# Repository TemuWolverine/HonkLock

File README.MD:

- [Electronics](#electronics)
  - [Brain board](#brain-board)
  - [Sensor Board](#sensor-board)
  - [Hardware](#hardware)
  - [Power](#power)
  - [Alternative power wiring](#alternative-power-wiring)
  - [ESP32 SuperMini Variants](#esp32-supermini-variants)
- [Blast Gate](#blast-gate)
  - [Gate](#gate)
  - [Sensor Box](#sensor-box)

Open-source automated blast gate system and tool detection system.

## Implementation
Currently, this is implemented using ESPHome with dependencies on Home Assistant to handle the syncing between gates.

Eventually, the goal is to have two versions - one with ESPHome, one standalone using something like ESP32-IDF/ESP-Now for communication between gates.
ESPHome's advantage is any buttons/remotes (Zigbee, ZWave, Matter, Wifi) connected to Home Assistant can be used to trigger each gate, as well as rapid development and deployment.

# Electronics
## Brain board 
[Schematic](PCB/HonkLockBrainboard.pdf)
| Item                                                                | Quantity | Note                                                                                                                                                                                                                                                                                                                                                                                                                                                             |
| ------------------------------------------------------------------- | -------- | ---------------------------------------------------------------------------------------------------------------------------------------------------------------------------------------------------------------------------------------------------------------------------------------------------------------------------------------------------------------------------------------------------------------------------------------------------------------- |
| [ESP32 S3 SuperMini](https://s.click.aliexpress.com/e/_c3BMFE2p)    | 1        | (Just about) Any ESP32 is going to work. The supermini's are just adorably tiny, inexpensive, and relatively easy to come across from a range of vendors. <br> The Supermini range also has an onboard WS2812 LED (GPIO48), meaning gate status can be indicated (red = closed, green = open) with the included LED.<br><br>**Other supermini variants <ins>except H2 (no wifi)</ins> _should_ work just fine, you will just need to adjust the code slightly.** |
| [0.1uF ceramic cap](https://www.lcsc.com/product-detail/C1711.html) | 2        | 0805/2012 package                                                                                                                                                                                                                                                                                                                                                                                                                                                |
| [1uF ceramic cap](https://www.lcsc.com/product-detail/C28323.html)  | 1        | 0805/2012 package                                                                                                                                                                                                                                                                                                                                                                                                                                                |
| [10k resistor](https://www.lcsc.com/product-detail/C17414.html)     | 2        | 0805/2012 package                                                                                                                                                                                                                                                                                                                                                                                                                                                |
| [33k resistor](https://www.lcsc.com/product-detail/C17633.html)     | 2        | 0805/2012 package                                                                                                                                                                                                                                                                                                                                                                                                                                                |
| [P82B715 (SOIC)](https://www.lcsc.com/product-detail/C2649394.html) | 1        | I2C Extender                                                                                                                                                                                                                                                                                                                                                                                                                                                     |
| [USB jack](https://www.lcsc.com/product-detail/C2765186.html)       | 1        | Ignore if not using USB for power                                                                                                                                                                                                                                                                                                                                                                                                                                |
| [5.1k resistor](https://www.lcsc.com/product-detail/C27834.html)    | 2        | Ignore if not using USB for power, 0805 size                                                                                                                                                                                                                                                                                                                                                                                                                     |
| [RJ-45 jack](https://www.lcsc.com/product-detail/C7501824.html)     | 1        |                                                                                                                                                                                                                                                                                                                                                                                                                                                                  |
| [3 pin JST XH](https://www.lcsc.com/product-detail/C157928.html)    | 1        | S3B-XH-A-LF                                                                                                                                                                                                                                                                                                                                                                                                                                                      |

## Sensor Board
[Schematic](PCB/HonkLockSensorBoard.pdf)
| Item                                                                | Quantity | Note                                   |
| ------------------------------------------------------------------- | -------- | -------------------------------------- |
| [MLX90393](https://www.lcsc.com/product-detail/C2649492.html)       | 1        | magnetometer for detecting tool on/off |
| [0.1uF ceramic cap](https://www.lcsc.com/product-detail/C1711.html) | 3        | 0805/2012 package                      |
| [1uF ceramic cap](https://www.lcsc.com/product-detail/C28323.html)  | 1        | 0805/2012 package                      |
| [10k resistor](https://www.lcsc.com/product-detail/C17414.html)     | 2        | 0805/2012 package                      |
| [33k resistor](https://www.lcsc.com/product-detail/C17633.html)     | 2        | 0805/2012 package                      |
| [P82B715 (SOIC)](https://www.lcsc.com/product-detail/C2649394.html) | 1        | I2C Extender                           |
| [RJ-45 jack](https://www.lcsc.com/product-detail/C7501824.html)     | 1        |                                        |

##  Hardware
| Item                                    | Quantity | Note                                              |
| --------------------------------------- | -------- | ------------------------------------------------- |
| 'Standard Servo'                        | 1        | I've used a MG996 clone                           |
| M2.5 heatset inserts, standoffs, screws |          | Design not 100% finalised                         |
| M4 and M5 Hardware                      |          | Design not 100% finalised                         |
| cat5 cable                          |          | For connecting the brainboard to the sensor board |

## Power
HonkLock is powered by any 5v1a USB brick - A or C.

## Alternative power wiring
If you'd rather have centralised power that runs out to each gate, you'll need to [calculate the wire required](https://www.omnicalculator.com/physics/wire-size).

## ESP32 SuperMini Variants  
There are a range of ESP32 "Supermini dev boards", most of which have identical pinouts, but not all are suitable.

| Variant | Suitable | Note                                                                                                                            |
| ------- | -------- | ------------------------------------------------------------------------------------------------------------------------------- |
| S3      | ✅        | Dual core Xtensa CPU, previous top of the line chip. Total overkill for this application, but so common that it isn't expensive |
| C3      | ✅        | A lower power/slower alternative to the S3 using a RISC-V singlecore CPU and has 2.4ghz wifi                                    |
| C3 Plus | ✅        | Seems to be a C3 with external antenna option                                                                                   |
| C6      | ✅        | Single core RISC-V chip, with Wifi 6 (2.4ghz) and thread/zigbee/matter support                                                  |
| H2      | ❌        | ESP32-H2 does not have Wifi at all, it has Bluetooth 5LE and thread/zigbee. Currently Wifi is a HonkLock requirement            |

# Blast Gate
## Gate

The current design is for *my* system, and thus is for 5" ducting. Fusion360 file provided for modification, eventually will model for different sizes.

* Blastgate: [Fusion360](CAD/BlastGate.f3z), [STEP](CAD/BlastGate.step), 3MF.
* Print in PETG, available on Makerworld with slicing settings built in.

## Sensor Box

* Sensor Box: [Fusion360](CAD/SensorBox.f3z), [STEP](CAD/SensorBox.step.step), 3MF.
* Print in PETG, available on Makerworld with slicing settings built in.
* Requires 4x M2.5 heatset inserts and M2.5 x 8mm screws

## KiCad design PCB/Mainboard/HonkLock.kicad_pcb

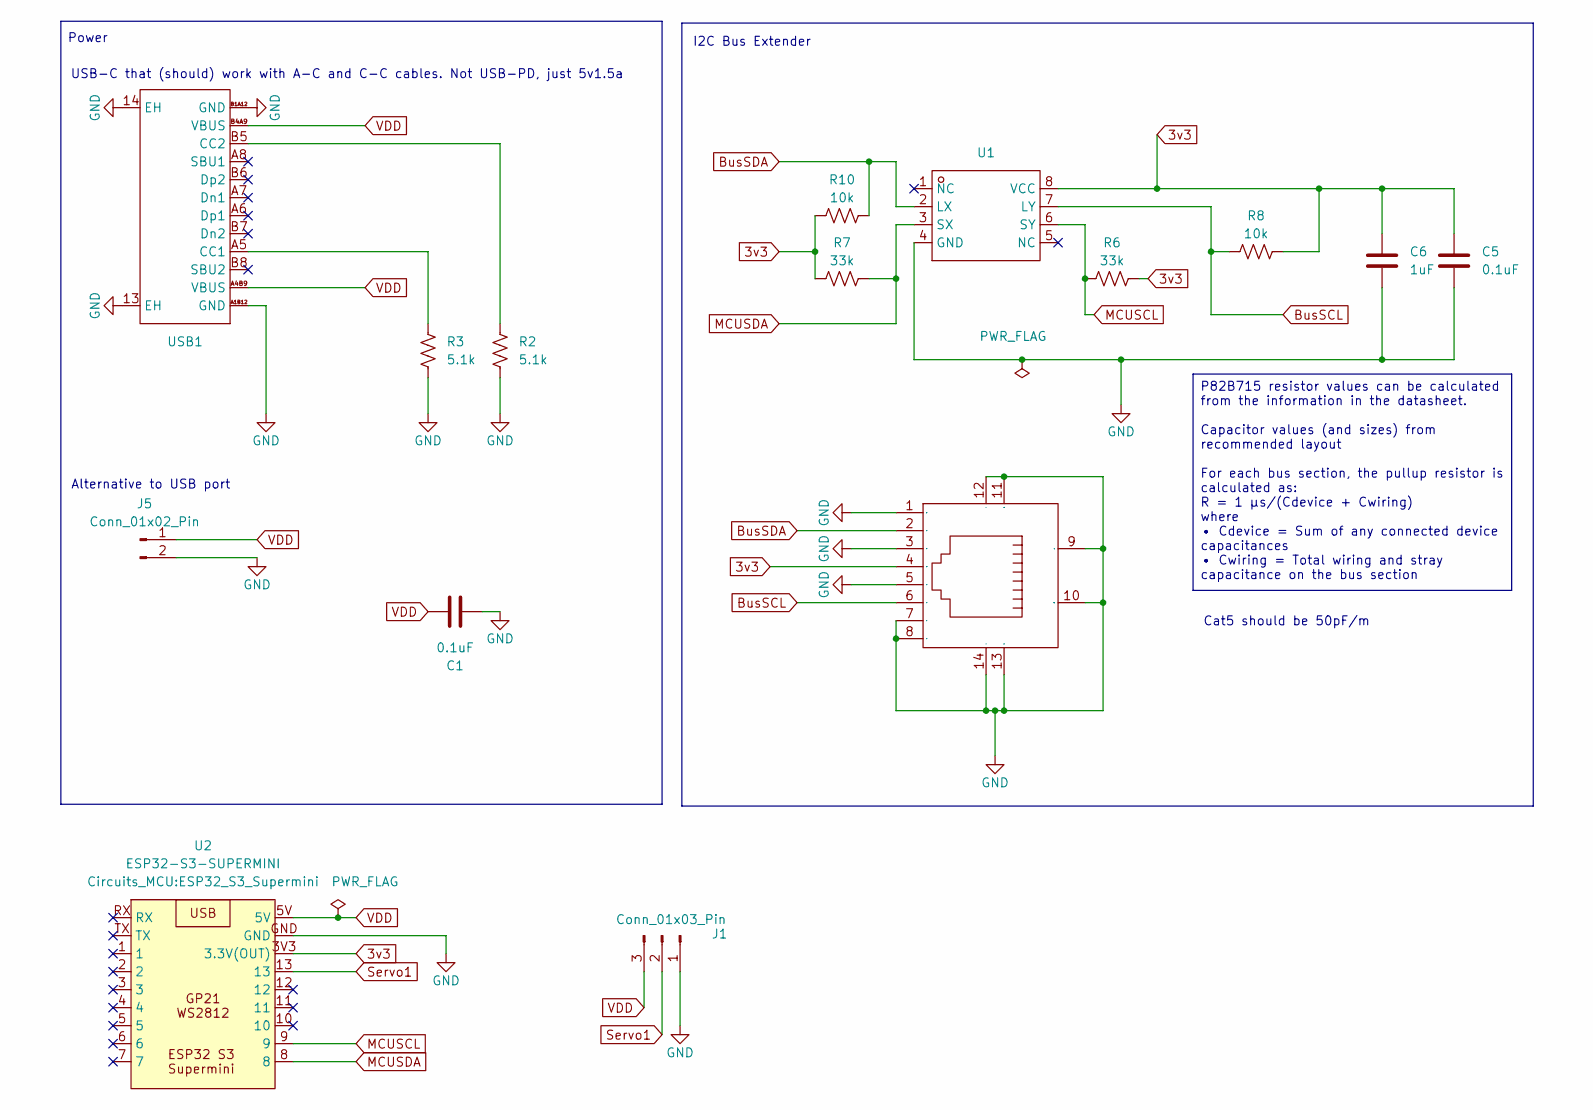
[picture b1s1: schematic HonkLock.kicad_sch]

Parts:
C1, C5: 0.1uF; C_0805_2012Metric
C6: 1uF; C_0805_2012Metric
J1: Conn_01x03_Pin; CONN-TH_S3B-XH-A-LF-SN
J5: Conn_01x02_Pin; PinHeader_1x02_P2.54mm_Vertical
R2, R3: 5.1k; R_0805_2012Metric
R6, R7: 33k; R_0805_2012Metric
R8, R10: 10k; R_0805_2012Metric
RJ1: RJ45-TH_HC-WK88-H16-DB; Manufacturer Part HC-WK88-H16-DB; LCSC Part Name 弯插 带LED 网口 RJ45-8P8C-16H半包 带灯 不锈钢壳 B款
U1: SOIC-8_L4.9-W3.9-P1.27-LS6.0-BL; Manufacturer Part P82B715DR; LCSC Part Name P82B715 I²C总线扩展器
U2: ESP32-S3-SUPERMINI; ESP32_S3_Supermini
USB1: USB-C-SMD_TYPE-C-16PIN-2MD-073; Manufacturer Part TYPE-C 16PIN 2MD(073); LCSC Part Name Type-C 母 卧贴

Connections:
3v3: C5.1, C6.1, R6.2, R7.1, R8.2, R10.1, RJ1.4, U1.8 (VCC), U2.3V3 (3.3V(OUT))
BusSCL: R8.1, RJ1.6, U1.7 (LY)
BusSDA: R10.2, RJ1.2, U1.2 (LX)
GND: C1.1, C5.2, C6.2, J1.1, J5.2, R2.1, R3.1, RJ1.1, RJ1.3, RJ1.5, RJ1.7, RJ1.8, RJ1.9, RJ1.10, RJ1.11 (+), RJ1.12 (-), RJ1.13 (+), RJ1.14 (-), U1.4 (GND), U2.GND, USB1.13 (EH), USB1.14 (EH), USB1.A1B12 (GND), USB1.B1A12 (GND)
MCUSCL: R6.1, U1.6 (SY), U2.9
MCUSDA: R7.2, U1.3 (SX), U2.8
unnamed: R3.2, USB1.A5 (CC1)
unnamed: R2.2, USB1.B5 (CC2)
Servo1: J1.2, U2.13
VDD: C1.2, J1.3, J5.1, U2.5V, USB1.A4B9 (VBUS), USB1.B4A9 (VBUS)

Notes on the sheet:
Alternative to USB port
Power
I2C Bus Extender
USB-C that (should) work with A-C and C-C cables. Not USB-PD, just 5v1.5a
Cat5 should be 50pF/m
P82B715 resistor values can be calculated from the information in the datasheet. Capacitor values (and sizes) from recommended layout For each bus section, the pullup resistor is calculated as: R = 1 μs/(Cdevice + Cwiring) where • Cdevice = Sum of any connected device capacitances • Cwiring = Total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

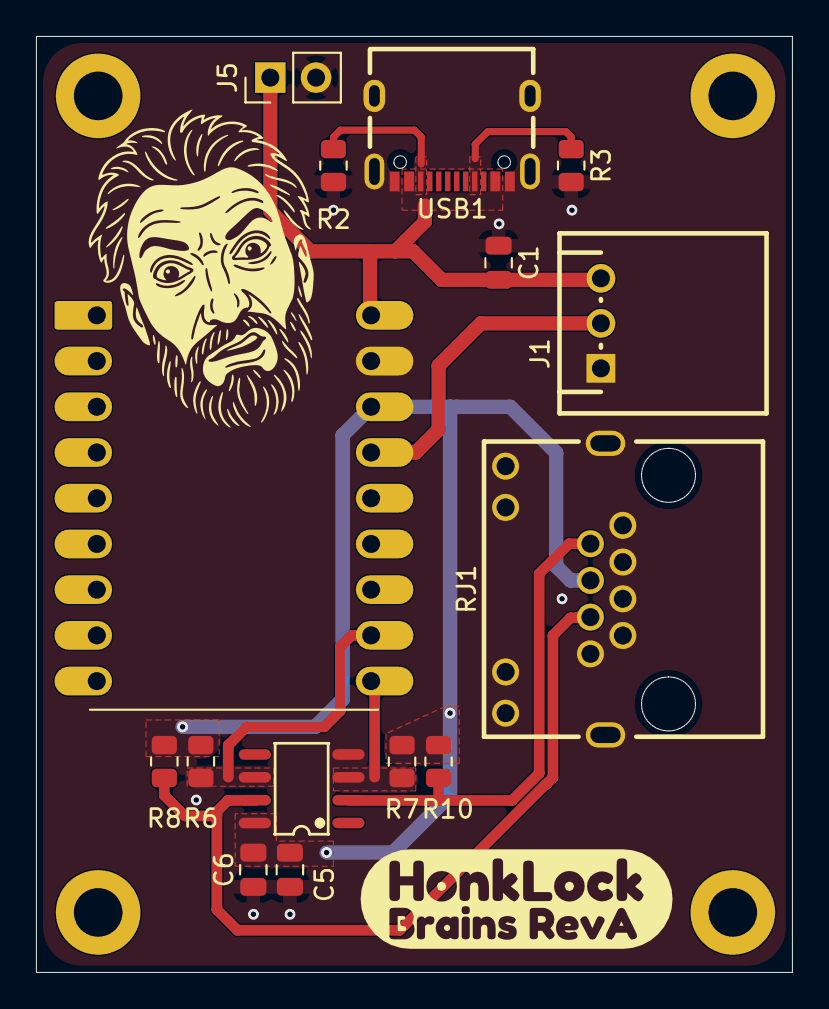
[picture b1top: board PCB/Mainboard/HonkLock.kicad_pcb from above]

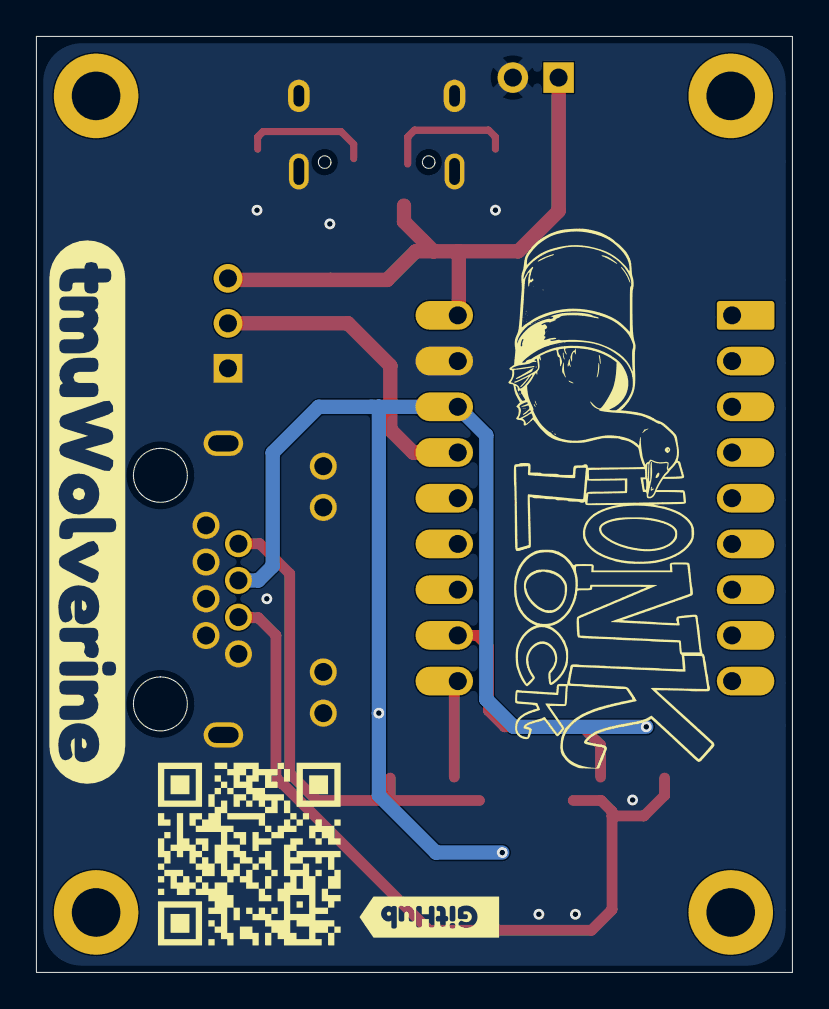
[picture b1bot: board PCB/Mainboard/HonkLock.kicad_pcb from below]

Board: 2 copper layers, 42.0 x 52.0 mm, 19 parts (3 on the bottom side), 10 nets.

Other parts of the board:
kobee-studio-6A97AAF5: Kobee Studio; kobee-studio-6A96C1A4
kobee-studio-6A97ABF4: Kobee Studio; kobee-studio-6A97ABF4
kobee-studio-6A97AC47: Kobee Studio; kobee-studio-6A97AC2D
kobee-studio-6A97AC75: Kobee Studio; kobee-studio-6A97AC75

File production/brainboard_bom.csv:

Designator,Footprint,Quantity,Value,LCSC Part #
"C1, C5",0805,2,0.1uF,
C6,0805,1,1uF,
J1,CONN-TH_S3B-XH-A-LF-SN,1,Conn_01x03_Pin,
J5,PinHeader_1x02_P2.54mm_Vertical,1,Conn_01x02_Pin,
"R10, R8",0805,2,10k,
"R2, R3",0805,2,5.1k,
"R6, R7",0805,2,33k,
RJ1,RJ45-TH_HC-WK88-H16-DB,1,~,C7501824
U1,SOIC-8_L4.9-W3.9-P1.27-LS6.0-BL,1,~,C2649394
USB1,USB-C-SMD_TYPE-C-16PIN-2MD-073,1,~,C2765186

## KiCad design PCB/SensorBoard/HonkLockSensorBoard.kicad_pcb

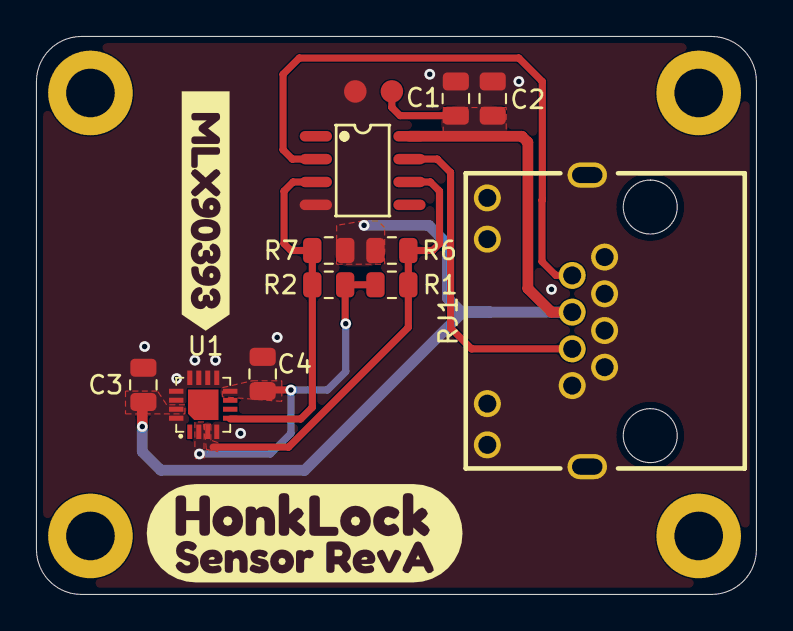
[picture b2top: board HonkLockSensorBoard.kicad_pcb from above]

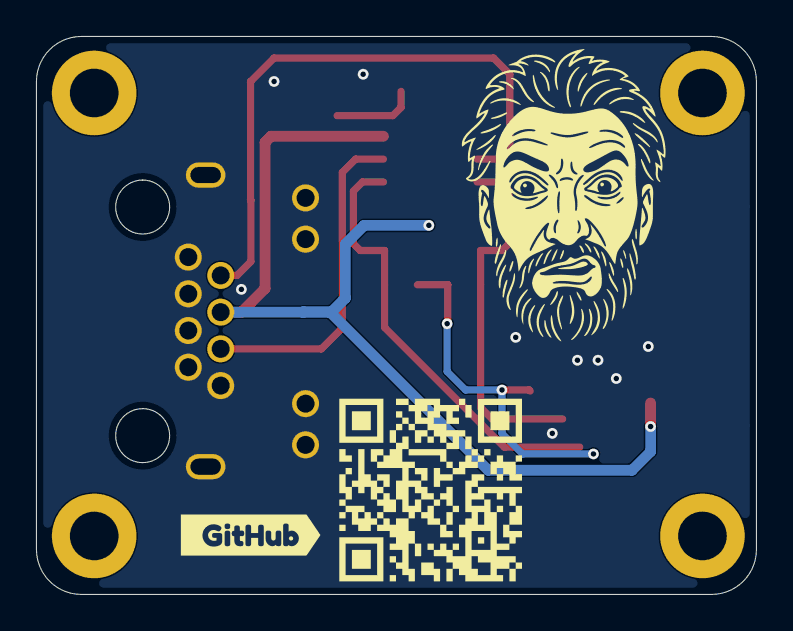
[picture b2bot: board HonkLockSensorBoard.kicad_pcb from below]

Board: 2 copper layers, 40.0 x 31.0 mm, 17 parts (2 on the bottom side), 7 nets.

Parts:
C1: 1uF; C_0805_2012Metric
C2, C3, C4: 0.1uF; C_0805_2012Metric
R1, R2: 10k; R_0805_2012Metric
R6, R7: 33k; R_0805_2012Metric
RJ1: RJ45-TH_HC-WK88-H16-DB
TP1, TP2: TestPoint; TestPoint-1.25mm
U1: VQFN-16_L3.0-W3.0-P0.50-BL-EP1.7
U2: SOIC-8_L4.9-W3.9-P1.27-LS6.0-BL
kobee-studio-6A96C2E0: Kobee Studio; kobee-studio-6A96C244
kobee-studio-6A97ABF4: Kobee Studio; kobee-studio-6A97ABF4
kobee-studio-6A97AC75: Kobee Studio; kobee-studio-6A97AC75
kobee-studio-6A97AD50: Kobee Studio; kobee-studio-6A96C1A4

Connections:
3v3: C1.1, C2.1, C3.1, R6.2, R7.1, RJ1.4, TP1.1 (1_1), U1.15 (VDD), U2.8 (VCC)
ControllerSCL: RJ1.6, U2.7 (LY)
ControllerSDA: RJ1.2, U2.2 (LX)
GND: C1.2, C2.2, C3.2, C4.1, RJ1.1, RJ1.3, RJ1.5, RJ1.7, RJ1.8, RJ1.9, RJ1.10, RJ1.11 (+), RJ1.12 (-), RJ1.13 (+), RJ1.14 (-), TP2.1 (1_1), U1.4 (N/C), U1.9 (N/C), U1.10 (N/C), U1.11 (A1), U1.12 (A0), U1.13 (VSS), U1.14 (N/C), U1.16 (N/C), U2.4 (GND)
SensorSCL: R1.2, R6.1, U1.3 (SCL/SCLK), U2.6 (SY)
SensorSDA: R2.1, R7.2, U1.5 (SDA/MOSI), U2.3 (SX)
VDDIO: C4.2, R1.1, R2.2, U1.2 (SENB/CS), U1.8 (VDD_IO)

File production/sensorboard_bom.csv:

Designator,Footprint,Quantity,Value,LCSC Part #
C1,0805,1,1uF,
"C2, C3, C4",0805,3,0.1uF,
"R1, R2",0805,2,10k,
"R6, R7",0805,2,33k,
RJ1,RJ45-TH_HC-WK88-H16-DB,1,~,C7501824
"TP1, TP2",TestPoint-1.25mm,2,TestPoint,
U1,VQFN-16_L3.0-W3.0-P0.50-BL-EP1.7,1,~,C2649492
U2,SOIC-8_L4.9-W3.9-P1.27-LS6.0-BL,1,~,C2649394

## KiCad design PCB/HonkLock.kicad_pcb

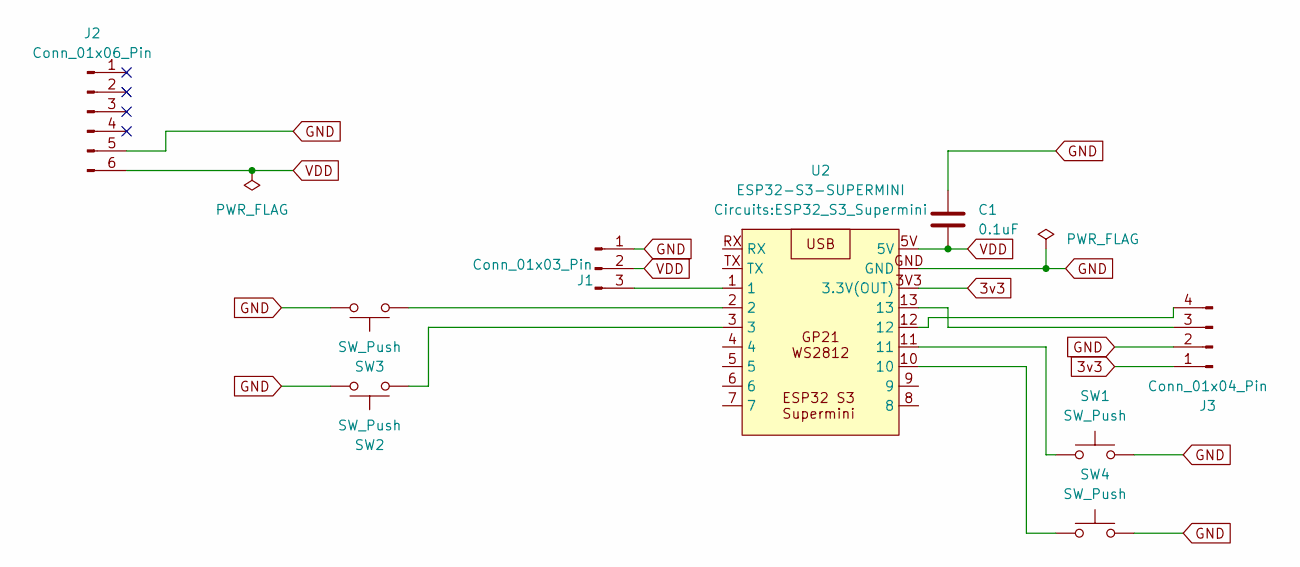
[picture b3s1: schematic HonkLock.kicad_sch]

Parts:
C1: 0.1uF; C_Disc_D3.0mm_W1.6mm_P2.50mm
J1: Conn_01x03_Pin; PinHeader_1x03_P2.54mm_Vertical
J2: Conn_01x06_Pin; PinHeader_1x06_P2.54mm_Vertical
J3: Conn_01x04_Pin; PinHeader_1x04_P2.54mm_Vertical
SW1, SW2, SW3, SW4: SW_Push; SW_PUSH_6mm
U2: ESP32-S3-SUPERMINI; ESP32_S3_Supermini

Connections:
3v3: J3.1, U2.3V3 (3.3V(OUT))
GND: C1.1, J1.1, J2.5, J3.2, SW1.2, SW2.2, SW3.2, SW4.2, U2.GND
unnamed: J1.3, U2.1
unnamed: J3.3, U2.13
unnamed: J3.4, U2.12
unnamed: SW1.1, U2.11
unnamed: SW2.1, U2.3
unnamed: SW3.1, U2.2
unnamed: SW4.1, U2.10
VDD: C1.2, J1.2, J2.6, U2.5V

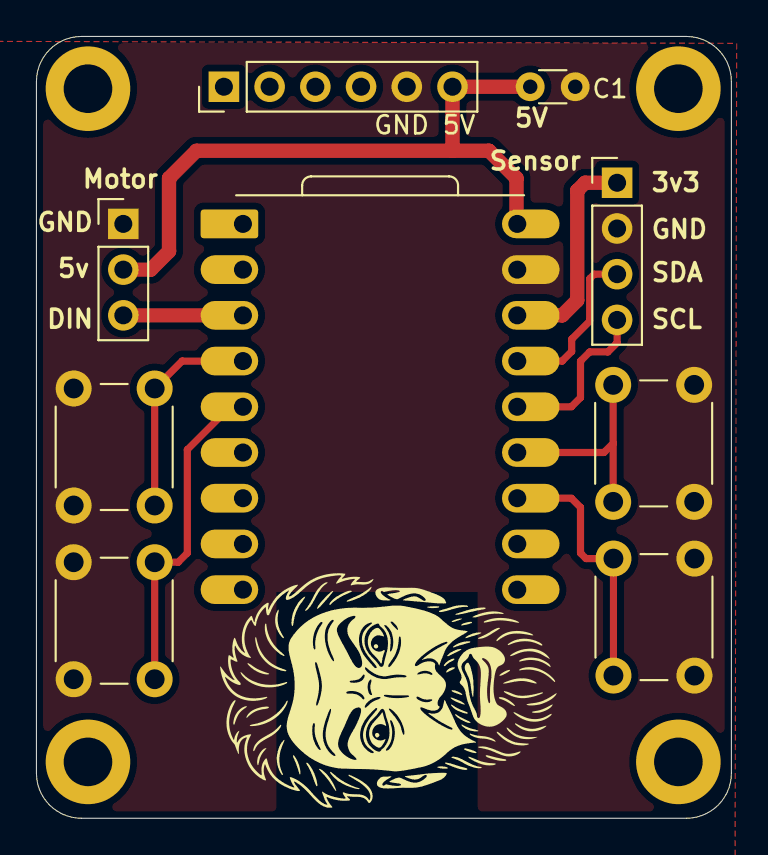
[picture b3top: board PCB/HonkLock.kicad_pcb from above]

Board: 2 copper layers, 38.6 x 43.4 mm, 10 parts (1 on the bottom side), 10 nets.

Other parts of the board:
kibuzzard-6A52EB91: G***; kibuzzard-6A52EB91
